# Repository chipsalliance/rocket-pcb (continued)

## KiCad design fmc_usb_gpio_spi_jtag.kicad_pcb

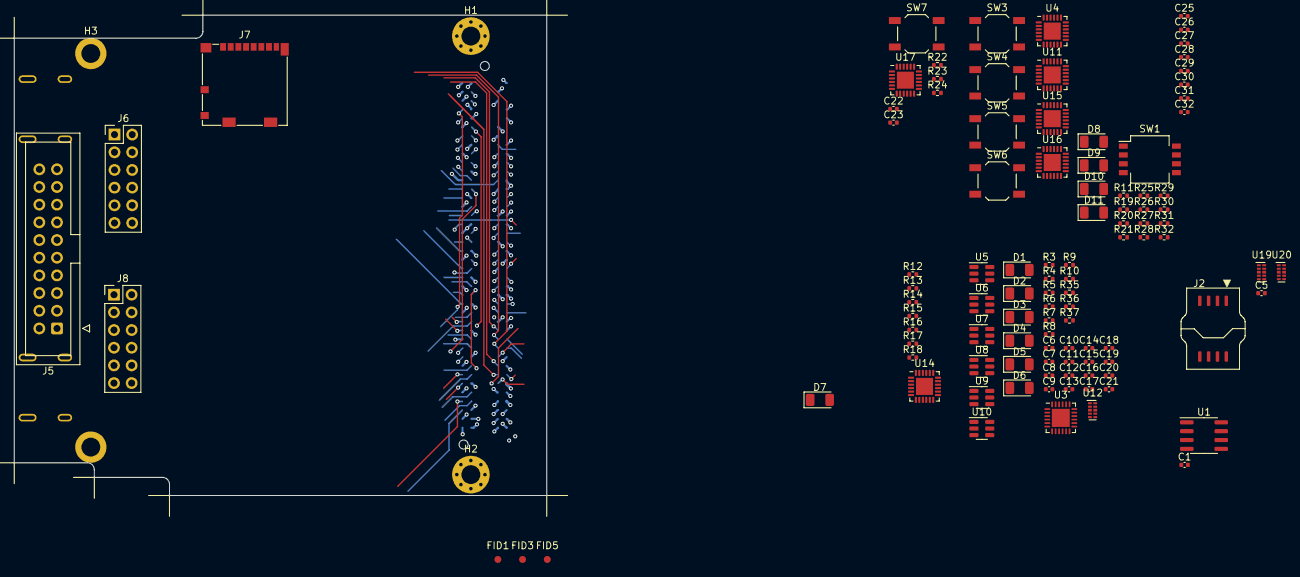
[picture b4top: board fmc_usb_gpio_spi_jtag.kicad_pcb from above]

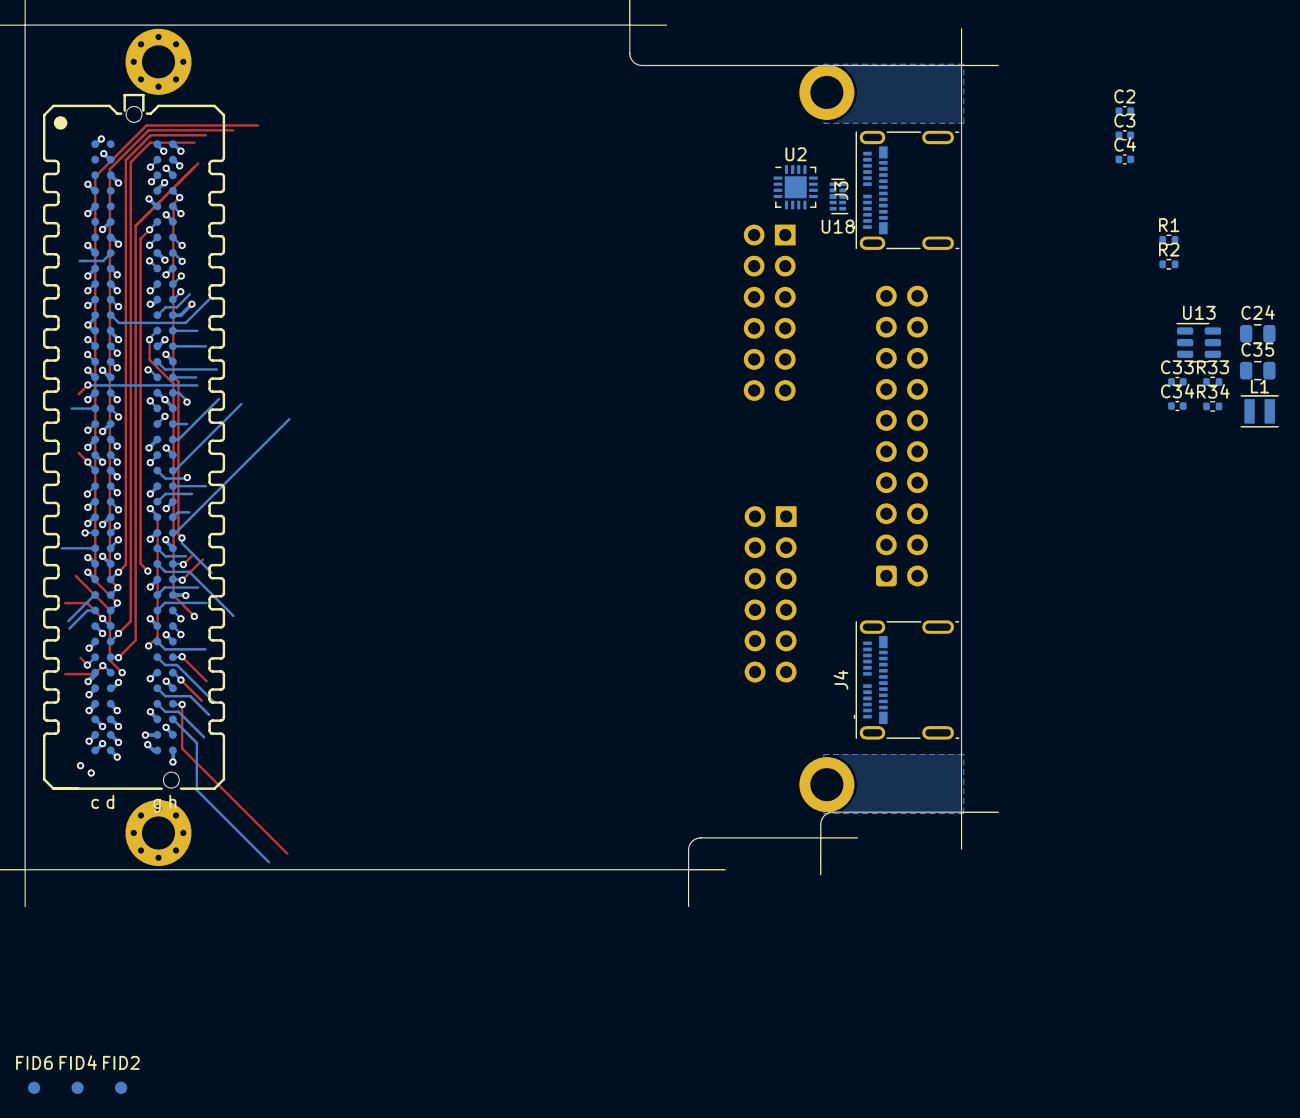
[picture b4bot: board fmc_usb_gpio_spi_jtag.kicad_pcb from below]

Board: 2 copper layers, 76.5 x 69.0 mm, 128 parts (21 on the bottom side), 94 nets.

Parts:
C1, C2, C5, C7, C8, C10, C11, C12, C13, C14, C15, C16, C17, C18, C19, C20, C21, C22, C23, C25, C26, C27, C28, C29, C30, C31, C32: 100n; C_0402_1005Metric
C3: 1u; C_0402_1005Metric
C4, C6, C9: 4.7u; C_0402_1005Metric
C24: 22uF ±20% 35V; C_0805_2012Metric
C33: 22n; C_0402_1005Metric
C34: 22p; C_0402_1005Metric
C35: 22uF; C_0805_2012Metric
D1, D2, D3, D4, D5, D6, D7, D8, D9, D10, D11: NCD1206Y1; LED_1206_3216Metric
FID1, FID2, FID3, FID4, FID5, FID6: 1mm; Fiducial_1mm_Mask2mm
H1, H2: M2.5; MountingHole_2.7mm_M2.5_Pad_Via
H3, H4: M2.5; MountingHole_2.7mm_M2.5_ISO14580_Pad
J1: SAMTEC_ASP-134604-01; Samtec_FMC_ASP-134604-01_4x40_P1.27mm
J2: ACA-SPI-004-K02; ACA-SPI-004
J3, J4: USB_C_Receptacle; USB_C_Receptacle_Molex_105450-0101
J5: Conn_JTAG_20; IDC-Header_2x10_P2.54mm_Vertical
J6, J8: PM2.54-2x6; PinHeader_2x06_P2.54mm_Vertical
J7: MOLEX 1040310811; microSD_HC_Molex_104031-0811
L1: 4.7uH ±20% 1.6A TFM252012ALMA4R7MTAA; L_Sunlord_SWPA252012S
R1, R2, R3, R4, R35: 5.1k; R_0402_1005Metric
R5, R6, R7, R8, R9, R10, R18, R29, R30, R31, R32: 10k; R_0402_1005Metric
R11, R12, R13, R14, R15, R16, R17, R19, R20, R21, R22, R23, R24, R25, R26, R27, R28, R37: 47k; R_0402_1005Metric
R33: 100k; R_0402_1005Metric
R34: 22k; R_0402_1005Metric
R36: 24k; R_0402_1005Metric
SW1: DSHP04TSGET; SW_DIP_SPSTx04_Slide_KingTek_DSHP04TS_W7.62mm_P1.27mm
SW3, SW4, SW5, SW6, SW7: TL3342F160QG; SW_SPST_TL3342
U1: M24C02-FMN; SOIC-8_3.9x4.9mm_P1.27mm
U2: STUSB03EQR; QFN_B03EQR_STM
U3: CP2104; QFN-24-1EP_4x4mm_P0.5mm_EP2.6x2.6mm
U4, U11, U14, U15, U16, U17: TXS02612RTWR; WQFN-24-1EP_4x4mm_P0.5mm_EP2.45x2.45mm
U5, U6, U7, U8, U9, U10: AIP74LVC1T45GB236TR; SOT-23-6
U12, U18, U19, U20: TPD4E02B04DQA; USON-10_2.5x1.0mm_P0.5mm
U13: MT2492; SOT-23-6

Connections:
/FMC/GA0: J1.C34 (Pin_34), U1.2 (E1)
/FMC/GA1: J1.D35 (d35), U1.1 (E0)
/FMC/SCL: J1.C30 (Pin_30), U1.6 (SCL)
/FMC/SDA: J1.C31 (Pin_31), U1.5 (SDA)
/GPIO/HVGPIO0: J6.1, U11.18 (DAT0B0)
/GPIO/HVGPIO1: J6.2, U11.16 (DAT1B0)
/GPIO/HVGPIO2: J6.3, U11.23 (DAT2B0)
/GPIO/HVGPIO3: J6.4, U11.22 (DAT3B0)
/GPIO/HVGPIO4: J6.5, U11.20 (CMDB0)
/GPIO/HVGPIO5: J6.6, U4.18 (DAT0B0)
/GPIO/HVGPIO6: J6.7, U4.16 (DAT1B0)
/GPIO/HVGPIO7: J6.8, U4.23 (DAT2B0)
/GPIO/HVGPIO8: J8.1, U4.22 (DAT3B0)
/GPIO/HVGPIO9: J8.2, U4.20 (CMDB0)
/GPIO/HVGPIO10: J8.3, U15.18 (DAT0B0)
/GPIO/HVGPIO11: J8.4, U15.16 (DAT1B0)
/GPIO/HVGPIO12: J8.5, U15.23 (DAT2B0)
/GPIO/HVGPIO13: J8.6, U15.22 (DAT3B0)
/GPIO/HVGPIO14: J8.7, U15.20 (CMDB0)
/GPIO/HVGPIO15: J8.8, U16.18 (DAT0B0)
/GPIO/HVGPIO16: D8.1 (K), R25.1, SW1.1, SW3.2, U16.16 (DAT1B0)
/GPIO/HVGPIO17: D9.1 (K), R26.1, SW1.2, SW4.2, U16.23 (DAT2B0)
/GPIO/HVGPIO18: D10.1 (K), R27.1, SW1.3, SW5.2, U16.22 (DAT3B0)
/GPIO/HVGPIO19: D11.1 (K), R28.1, SW1.4, SW6.2, U16.20 (CMDB0)
/JTAG/SRST: J5.15 (~SRST), R23.2, SW7.2, U17.7 (DAT1A)
/JTAG/TCK: J5.9 (TCK), U17.9 (CLKA)
/JTAG/TDI: J5.5 (TDI), U17.4 (CMDA)
/JTAG/TDO: J5.13 (TDO), U17.3 (DAT3A)
/JTAG/TMS: J5.7 (TMS), U17.1 (DAT2A)
/JTAG/TRST: J5.3 (~TRST), R24.2, U17.6 (DAT0A)
/SDIO/SD_CLK: J7.5 (CLK), U14.19 (CLKB0)
/SDIO/SD_CMD: J7.3 (CMD), R17.1, U14.20 (CMDB0)
/SDIO/SD_DAT0: J7.7 (DAT0), R13.1, U14.18 (DAT0B0)
/SDIO/SD_DAT1: J7.8 (DAT1), R14.1, U14.16 (DAT1B0)
/SDIO/SD_DAT2: J7.1 (DAT2), R15.1, U14.23 (DAT2B0)
/SDIO/SD_DAT3: J7.2 (DAT3/CD), R16.1, U14.22 (DAT3B0)
/SPI FLASH/SPI_FLASH.CLK: J2.6, U20.2 (IO2), U20.9 (NC)
/SPI FLASH/SPI_FLASH.CS: J2.1, U19.1 (IO1), U19.10 (NC)
/SPI FLASH/SPI_FLASH.DI: J2.5, U20.4 (IO3), U20.7 (NC)
/SPI FLASH/SPI_FLASH.DO: J2.2, U19.2 (IO2), U19.9 (NC)
/SPI FLASH/SPI_FLASH.~HOLD: J2.7, U20.1 (IO1), U20.10 (NC)
/SPI FLASH/SPI_FLASH.~WP: J2.3, U19.4 (IO3), U19.7 (NC)
/UART/CP_IO0: U3.14 (TXT/GPIO.0), U5.4 (B)
/UART/CP_IO1: U3.13 (RXT/GPIO.1), U6.4 (B)
/UART/CP_IO2: U3.12 (RS485/GPIO.2), U7.4 (B)
/UART/CP_IO3: U3.11 (GPIO.3), U8.4 (B)
/UART/CP_SUSP: U3.17 (SUSPEND), U9.4 (B)
/UART/CP_~SUSP: U3.15 (~SUSPEND), U10.4 (B)
/USB/D+: J3.A6 (D+), J3.B6 (D+), U2.11 (D+), U18.4 (IO3), U18.7 (NC)
/USB/D-: J3.A7 (D-), J3.B7 (D-), U2.10 (D-), U18.5 (IO4), U18.6 (NC)
GND: C1.2, C2.2, C3.2, C4.2, C5.2, C6.2, C7.2, C8.2, C9.2, C10.2, C11.2, C12.2, C13.2, C14.2, C15.2, C16.2, C17.2, C18.2, C19.2, C20.2, C21.2, C22.2, C23.2, C24.2, C25.2, C26.2, C27.2, C28.2, C29.2, C30.2, C31.2, C32.2, C35.2, H1.1, H2.1, H3.1, H4.1, J1.C1 (Pin_1), J1.C4 (Pin_4), J1.C5 (Pin_5), J1.C8 (Pin_8), J1.C9 (Pin_9), J1.C12 (Pin_12), J1.C13 (Pin_13), J1.C16 (Pin_16), J1.C17 (Pin_17), J1.C20 (Pin_20), J1.C21 (Pin_21), J1.C24 (Pin_24), J1.C25 (Pin_25), J1.C28 (Pin_28), J1.C29 (Pin_29), J1.C32 (Pin_32), J1.C33 (Pin_33), J1.C36 (Pin_36), J1.C38 (Pin_38), J1.C40 (Pin_40), J1.D2 (d2), J1.D3 (d3), J1.D6 (d6), J1.D7 (d7), J1.D10 (d10), J1.D13 (d13), J1.D16 (d16), J1.D19 (d19), J1.D22 (d22), J1.D25 (d25), J1.D28 (d28), J1.D37 (d37), J1.D39 (d39), J1.G1 (g1), J1.G4 (g4), J1.G5 (g5), J1.G8 (g8), J1.G11 (g11), J1.G14 (g14), J1.G17 (g17), J1.G20 (g20), J1.G23 (g23), J1.G26 (g26), J1.G29 (g29), J1.G32 (g32), J1.G35 (g35), J1.G38 (g38), J1.G40 (g40), J1.H2 (h2), J1.H3 (h3), J1.H6 (h6), J1.H9 (h9), J1.H12 (h12), J1.H15 (h15), J1.H18 (h18), J1.H21 (h21), J1.H24 (h24), J1.H27 (h27), J1.H30 (h30), J1.H33 (h33), J1.H36 (h36), J1.H39 (h39), J2.4, J3.A1 (GND), J3.A12 (GND), J3.B1 (GND), J3.B12 (GND), J3.S1 (SHIELD), J4.A1 (GND), J4.A12 (GND), J4.B1 (GND), J4.B12 (GND), J4.S1 (SHIELD), J5.4 (GND), J5.6 (GND), J5.8 (GND), J5.10 (GND), J5.12 (GND), J5.14 (GND), J5.16 (GND), J5.18 (GND), J5.20 (GND), J6.9, J6.10, J7.6 (VSS), J7.9 (DET_B), J7.11 (SHIELD), J8.9, J8.10, R1.1, R2.1, R3.1, R4.1, R5.2, R6.2, R7.2, R8.2, R9.2, R10.2, R11.1, R12.1, R19.1, R20.1, R21.1, R22.1, R34.1, R37.1, SW1.5, SW1.6, SW1.7, SW1.8, SW3.1, SW4.1, SW5.1, SW6.1, SW7.1, U1.3 (E2), U1.4 (VSS), U1.7 (~WC), U2.6 (GND), U3.2 (GND), U3.25 (GND), U4.2 (GND), U4.11 (GND), U4.25 (GND), U5.2 (GND), U5.5 (DIR), U6.2 (GND), U6.5 (DIR), U7.2 (GND), U7.5 (DIR), U8.2 (GND), U8.5 (DIR), U9.2 (GND), U9.5 (DIR), U10.2 (GND), U10.5 (DIR), U11.2 (GND), U11.11 (GND), U11.25 (GND), U12.3 (G), U12.8 (G), U13.1 (GND), U14.2 (GND), U14.11 (GND), U14.25 (GND), U15.2 (GND), U15.11 (GND), U15.25 (GND), U16.2 (GND), U16.11 (GND), U16.25 (GND), U17.2 (GND), U17.11 (GND), U17.25 (GND), U18.3 (G), U18.8 (G), U19.3 (G), U19.8 (G), U20.3 (G), U20.8 (G)
unnamed: C3.1, U2.12 (VTRM)
unnamed: C4.1, J3.A4 (VBUS), J3.A9 (VBUS), J3.B4 (VBUS), J3.B9 (VBUS), U2.14 (VBUS)
unnamed: D1.2 (A), U5.3 (A)
unnamed: D1.1 (K), R5.1
unnamed: D2.2 (A), U6.3 (A)
unnamed: D2.1 (K), R6.1
unnamed: D3.2 (A), U7.3 (A)
unnamed: D3.1 (K), R7.1
unnamed: D4.2 (A), U8.3 (A)
unnamed: D4.1 (K), R8.1
unnamed: D5.2 (A), U9.3 (A)
unnamed: D5.1 (K), R9.1
unnamed: D6.2 (A), U10.3 (A)
unnamed: D6.1 (K), R10.1
unnamed: D7.1 (K), R18.2
unnamed: D8.2 (A), R29.2
unnamed: D9.2 (A), R30.2
unnamed: D10.2 (A), R31.2
unnamed: D11.2 (A), R32.2
unnamed: J1.D30 (d30), J1.D31 (d31)
unnamed: J3.A5 (CC1), R1.2
unnamed: J3.B5 (CC2), R2.2
unnamed: J4.A5 (CC1), R3.2
unnamed: J4.B5 (CC2), R4.2
unnamed: J4.A4 (VBUS), J4.A9 (VBUS), J4.B4 (VBUS), J4.B9 (VBUS), R36.2
unnamed: J7.10 (DET_A), R18.1
unnamed: R36.1, R37.2, U3.8 (VBUS)
unnamed: C9.1, U3.16 (VPP)
unnamed: R35.1, U3.9 (~RST)
unnamed: R19.2, U4.9 (CLKA), U4.24 (SEL)
unnamed: R11.2, U11.9 (CLKA), U11.24 (SEL)
unnamed: J4.A6 (D+), J4.B6 (D+), U3.3 (D+), U12.4 (IO3), U12.7 (NC)
unnamed: J4.A7 (D-), J4.B7 (D-), U3.4 (D-), U12.5 (IO4), U12.6 (NC)
unnamed: C33.2, U13.6 (BST)
unnamed: C34.1, R33.1, R34.2, U13.4 (FB)
unnamed: C33.1, L1.1, U13.2 (SW)
unnamed: R12.2, U14.24 (SEL)
unnamed: R20.2, U15.9 (CLKA), U15.24 (SEL)
unnamed: R21.2, U16.9 (CLKA), U16.24 (SEL)
unnamed: R22.2, U17.24 (SEL)
P3V3: C25.1, C26.1, C27.1, C28.1, C29.1, C30.1, C31.1, C32.1, J6.11, J6.12, J8.11, J8.12, R25.2, R26.2, R27.2, R28.2, R29.1, R30.1, R31.1, R32.1, U4.5 (VCCA), U4.17 (VCCB1), U4.21 (VCCB0), U11.5 (VCCA), U11.17 (VCCB1), U11.21 (VCCB0), U15.5 (VCCA), U15.17 (VCCB1), U15.21 (VCCB0), U16.5 (VCCA), U16.17 (VCCB1), U16.21 (VCCB0)
P12V: C24.1, U13.3 (IN), U13.5 (EN)
VDD: C1.1, C2.1, C5.1, C6.1, C7.1, C8.1, C10.1, C11.1, C12.1, C13.1, C14.1, C15.1, C16.1, C17.1, C18.1, C19.1, C20.1, C21.1, C22.1, C23.1, C34.2, C35.1, D7.2 (A), J1.C35 (Pin_35), J1.C37 (Pin_37), J1.C39 (Pin_39), J1.D32 (d32), J1.D36 (d36), J1.D38 (d38), J1.D40 (d40), J1.G39 (g39), J1.H40 (h40), J2.8, J5.1 (VTREF), J7.4 (VDD), L1.2, R13.2, R14.2, R15.2, R16.2, R17.2, R23.1, R24.1, R33.2, R35.2, U1.8 (VCC), U2.8 (RSEL), U2.15 (VIF), U3.5 (VIO), U3.6 (VDD), U3.7 (REGIN), U5.1 (VCCA), U5.6 (VCCB), U6.1 (VCCA), U6.6 (VCCB), U7.1 (VCCA), U7.6 (VCCB), U8.1 (VCCA), U8.6 (VCCB), U9.1 (VCCA), U9.6 (VCCB), U10.1 (VCCA), U10.6 (VCCB), U14.5 (VCCA), U14.17 (VCCB1), U14.21 (VCCB0), U17.5 (VCCA), U17.17 (VCCB1), U17.21 (VCCB0)

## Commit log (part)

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2023-03-31 README.md: fix link to fmc_basic_peripheral
2023-03-31 README.md: format markdown table
2023-04-03 *.kicad_pcb: update layout, change cp2104 to USB bus powered
2023-04-03 sdio.kicad_sch: change sdcard detect LED resistor to 6.8k Ohm
2023-04-03 uart.kicad_sch: for easy wiring, swap D5 and D6
2023-04-03 usb.kicad_sch: rename USB_VBUS to USB_FS_VBUS
2023-04-03 *.kicad_pcb: update layout for LED swap
2023-04-07 *.kicad_pcb: add dummy pattern
2023-04-07 fpga/vcu118/*: Add FPGA project for rough testing of FMC boards
2023-04-07 uart.kicad_sch: replace cp2104 with ch9102f
    After testing, cp2104 is unstable at the moment of power-on,
    so it is replaced with ch9102f to fix this issue.
2023-04-07 *.kicad_sch: update footprint for QFN*
2023-04-10 top.xdc: Fix pin mapping issue for UART xdc
    - Fix UART communication issue by swapping `uart_rx` and `uart_tx` pins in `top.xdc`
2023-04-10 fmc.kicad_sch: Improve FMC peripheral schematic
    - Add annotation for UART crossing
2023-04-23 jtag.kicad_sch: move VADJ annotation text
    - Update and improve JTAG schematic file
2023-04-23 *pcb: Update PCB layout design for FMC peripherals.
    - Connect user RESET to CH9102F
    - Implement significant changes to [fmc_basic_peripheral/fmc_usb_gpio_spi_jtag.kicad_pcb]
    - Fix known bugs within affected files
    - Enhance overall user experience and functionality
2023-04-23 usb.kicad_sch: add LED for usb VBUS power and ~{SUSP}
    - add orange LED for usb VBUS
    - add yellow LED for usb ~{SUSP}
2023-04-23 uart.kicad_sch: change D5 to NCD1206Y1
    - fix color of D5
2023-04-24 usb.kicad_sch: add matching resistor to STUSB03E
2023-04-24 *.kicad_pcb: add matching resistor to STUSB03E
    - update layout of STUSB03E
    - DRC clean
2023-04-24 *.kicad_pcb: bump version to 1.0.5
    - DRC clean, update version to match the schematic
2023-05-09 *.kicad_pcb: clean DRC for kicad 7.0.2
2023-05-09 *.kicad_pro: ignore silk_over_copper check
2023-05-09 fmc_basic_peripheral: rotate SW1, bump to 1.0.6
2023-05-11 fmc_basic_peripheral/fpga/vcu118/.gitignore: ignore .cache
2023-05-11 fmc_basic_peripheral/*/openocd.cfg: use new command
2023-05-17 fmc_basic_peripheral/*/top.v: fix reset and mode switch logic
2023-05-17 fmc_basic_peripheral/*/top.v: add sdio xdc and test square wave
2023-05-17 .gitmodules: update submodule link
2023-05-17 uart.kicad_sch: merge CP_IO into GPIO
2023-05-17 gpio.kicad_sch: change GPIO range to [0..23]
2023-05-17 README.md: add index
2023-05-17 *.kicad_sch: fix mounting hole footprint
2023-05-17 *.kicad_sch: expand gpio to [0..31]
2023-05-17 *.kicad_pcb: pre-place devices
    Pre place user key, led, micro-sd socket, etc.
2023-05-17 *.*: finish flash and sdio layout
2023-05-17 Vowstar_Interface*: add stusb3 symbol and footprint
2023-05-17 usb.kicad_sch: add stusb fs transceiver symbol
2023-05-17 template/chipsalliance.kicad_wks: add template of chipsalliance
2023-05-17 sdio.kicad_sch: add SDIO bus lable
2023-05-17 *.kicad_pcb: apply schematic change, fix jtag
2023-05-17 *.kicad_pcb: add stackup table
2023-05-17 *.kicad_pcb: import GX0011D to pcb
2023-05-17 fmc.kicad_sch: fix power flag
2023-05-17 */*: change lib id to CHIPSAlliance
2023-05-17 *.kicad_wks: remove useless TEXT
2023-05-17 uart.kicad_sch: reorder bus alias
2023-05-17 spi_flash.kicad_sch: finished spi flash schematic
2023-05-17 jtag.kicad_sch: fix TRST and SRST polarity
2023-05-17 *.kicad_pcb: add via sealring at board edge
2023-05-17 library: add mounting holes and fiducials
2023-05-17 {library,sdio.kicad_sch}: fix microSD contact style
    Change the microSD contact on the opposite side to a dashed line
2023-05-17 *.kicad_pcb: fix bug of U26, disconnect the CMDA pin
2023-05-17 usb.kicad_sch: fix USB polarity of D+ and D-
2023-05-17 power.kicad_sch: change voltage to 5V
2023-05-17 *.kicad_pcb: import and fix power netlist
2023-05-17 fmc_usb_gpio_spi_jtag.kicad_sch: update fiducial and holes
2023-05-17 *.kicad_sch: fix sheet pin type
2023-05-17 library: add missing GND pin of TXS02612RTWR
2023-05-17 fmc_usb_gpio_spi_jtag.*: update top symbol
2023-05-17 CMakeLists.txt: add python-bom file to PROJECT_PRODUCTION_FILES
2023-05-17 spi_flash.kicad_sch: add signal annotation
2023-05-17 *.kicad_sch: fix GPIO sheet pins
2023-05-17 *{dru,pcb,pro}: fix DRC errors
2023-05-17 */*: restruct project, move * to fmc_basic_peripheral
2023-05-17 *.kicad_dru: fix design rule, add usb net class design rule
2023-05-17 *.kicad_pcb: finish 5V power layout
2023-05-17 fmc.kicad_sch: relink symbol form libraries
2023-05-17 *.kicad_pcb: complete the JTAG signal layout
2023-05-17 sym-lib-table: add mechanical library
2023-05-17 *.kicad_sch: add schematic placeholder of gpio,jtag,power,sdio,spi
2023-05-17 jtag.kicad_sch: use TXS02612RTWR as level shifter
2023-05-17 sym-lib-table: add Logic and Regulator_Switching
2023-05-17 *.kicad_pcb: import netlist form schematic
2023-05-17 power.kicad_sch: add MT2492 power IC
2023-05-17 *.*: add design rule file of PCB
2023-05-17 *.kicad_pcb: add teardrop and enhanced power
2023-05-17 *.kicad_pcb: import schematic to PCB
2023-05-17 fmc_usb_gpio_spi_jtag.kicad_sch: change mounting holes
2023-05-17 *.*: bump version to 1.0.1
2023-05-17 *.kicad_sch: connect GX0011 thermometer sensor
2023-05-17 {library,fp-lib-table}: add FMC MountingHole library
2023-05-17 *.kicad_sch: add CHIPSAlliance_ prefix for footprint
2023-05-17 *.kicad_sch: make vadj textbox wider
2023-05-17 gpio.kicad_sch: use TXS02612RTWR as level shifter
2023-05-17 jtag.kicad_sch: add Conn_JTAG_20
2023-05-17 library: add new symbols of power/levelshifter/connectors
2023-05-17 usb.kicad_sch: finished usb schematic
2023-05-17 i3c.kicad_sch: add i3c bus label
2023-05-17 *.kicad_pcb: annotate PMODs and keys
    Optimize silk screen, add QR code
2023-05-17 gpio.kicad_sch: fix bug of U26, disconnect the CMDA pin
2023-05-17 *.kicad_sch: ERC clean
2023-05-17 fmc.kicad_sch: add signal annotation, use new template
2023-05-17 */*: Initial commit
2023-05-17 {*-table,library}: add CHIPSAlliance_ prefix
2023-05-17 uart.kicad_sch: update usb connector symbol
2023-05-17 *.kicad_pcb: pre-placed components
2023-05-17 fmc.kicad_sch: add hierarchical_label for power and ground
2023-05-17 Vowstar_*->library: move libraries to gitmodule
2023-05-24 fmc_basic_peripheral/library: fix submodule link
2023-12-07 .gitmodules: fix library submodule name
    - Change [submodule "library"] to [submodule "fmc_basic_peripheral/library"]
2023-12-07 fmc_basic_peripheral: fix GPIO PMOD schematic
    - Fix PMOD symbol pin order
    - Followed Digilent Pmod Interface Specification 1.2.0
2023-12-07 fmc_basic_peripheral: bump to 1.0.7, fix ERC
2023-12-07 pmod_microsd: init project, draft schematic
    - Add initial schematic with Sifive's proposed changes
2023-12-08 pmod_microsd/{fp,sym}-lib-table: add Power_Protection library
    - Add CHIPSAlliance_Package_SON footprint library to project
    - Add CHIPSAlliance_Power_Protection symbol library to project
2023-12-08 pmod_microsd: annotate the components
    - Annotate various components so that components have unique references
2023-12-08 pmod_microsd: add PWR_FLAG to VDD and GND, ERC clean
    - Add PWR_FLAG to 3P3V (VDD)
    - Add PWR_FLAG to GND
    - ERC Clean
2023-12-09 pmod_microsd/*.kicad_pcb: PCB outline definition
    - Complete PCB outline and size definition
    - Arrange silk screen
    - Arrange text objects
2023-12-09 pmod_microsd/*.kicad_pcb: Complete PCB layout and routing
    - Complete PCB layout
    - Complete PCB routing
    - Complete PCB silk screen placement
    - LVS comparison successful
    - DRC cleared
2023-12-09 pmod_microsd: add CMakeLists.txt to generate production data
    - cmake -B build -G Ninja
    - cmake --build build
2023-12-09 pmod_microsd/README.md: Add brief documentation
    - Add a brief description
    - Add pin mapping relationship about PMOD and VCU118
    - Added documentation for LED indication
    - Add special pin description
2023-12-09 pmod_microsd/README.md: fix error in LED description
    - Swap power and card detection description
2023-12-09 fmc_basic_peripheral: Update CMakeLists for KiCad Upgrade
    This commit updates the CMakeLists.txt file in the
    fmc_basic_peripheral project to align with the latest KiCad
    version. Changes include:
    1. Modified gerber export command to include 'User.Drawings' in
    the layer list.
    2. Adjusted drill export command to use '--generate-map' and
2023-12-11 .gitignore: exclude build artifacts and python venv
    - Add /bom, /build, /production directories
    - Exclude Python virtual env folder .venv/
2024-02-28 fmc_basic_peripheral: Migrate to kicad8
    - Migrate schematics to kicad8
    - Migrate PCB to kicad8
    - Clean ERC
    - Clean LVS and DRC
2024-02-28 fmc_basic_peripheral: add erc and drc to CMakeLists.txt
    - add erc and drc custom_target and custom_command
    - use these command to check erc and drc:
    cmake -G Ninja -B build
    cmake --build build --target erc
    cmake --build build --target drc
2024-02-28 fmc_basic_peripheral: update SOT-23-5 footprint and fix DRC
2024-02-28 github: Automate CI process for all subdirectories
    - Replaced static directory path with dynamic listing
    - Implemented loop to process all subdirectories
    - Each directory now runs full build and validation sequence
2024-02-29 pmod_microsd: Optimize bom export
2024-02-29 github: Update tag base name extraction in release workflow
    - Modify logic to extract base name from Git tag
    - Replace deprecated set-output with GITHUB_ENV for variables
2024-03-01 ADD: add Gerber files
2024-03-03 fmc_basic_peripheral: require kicad 8
    - README.md: kicad 7 -> kicad 8
2024-03-04 fpga_candelabra: rename project
2024-03-07 Candelabra: Place all FPGA symbols
2024-03-19 Bump library
2024-03-21 FIX: fix C7 placement issue
2024-04-07 fpga_candelabra: reorganize fpga io and mgt by SLR
    - Rename sch sheets
    - Add prelimary DDR and PCIE Bank/Quad allocation
2024-04-09 pmod_microsd/CMakeLists.txt: require kicad 8
    - bump kicad 7 -> kicad 8
2024-04-09 REFACTOR: rename with prefix 'pmod_'
2024-04-09 ADD: add project source code
2024-04-21 fpga_candelabra: fix minor issues in ddr sch
2024-04-21 fpga_candelabra: add clock pll, refactor fmc power
2024-04-21 fpga_candelabra: bump library
2024-05-26 fmc_sdram: Add SDRAM FMC
2024-05-30 README.md: Update README with FMC_SDRAM project introduction
    - Added a new project FMC_SDRAM to the project introduction table.
2024-06-22 fmc_sdram: fix package for SN74AVCH16T245GR
2024-11-01 fpga_candelabra: major revision
    * Finish DDR4 & QSFP+ & PCIe layout
    * Change FMC to LPC
    * Add mikroBUS extension
    * 12V input & PDN updates
    * FPGA config updates
2024-11-11 fpga_candelabra: fix cmake layers
2024-12-09 fpga_candelabra: add ground copper pours for DFM
2025-01-01 fpga_candelabra: fix wrong VCCINT pin number
2025-01-18 fpga_candelabra: use LMK03328 PLL
2025-02-04 fpga_candelabra: more bugfixes & improvements for rev 0.2.0
    - Add Digilent JTAG-SMT2-NC onboard
    - Add fan controller & 4pin fan header
    - Use 9pin header for USB2.0
    - Misc fixes for structure
2026-04-06 fpga_candelabra: exclude pcie edge conn from BOM
2026-04-06 fpga_candelabra: update to kicad 9.0
2026-04-06 github: upgrade CI to kicad 10 and ubuntu 24.04, fix BOM export
2026-04-06 gitignore: add .history directory
2026-04-06 fmc_sdram: fix DRC violations and adjust thermal relief settings
2026-04-06 library: update submodule to fix remaining .wrl references
2026-04-06 github: restore apt cache for kicad packages
2026-05-21 fmc_sdram: tie dqm level shifter dir pins to vadj and fix pcb
2026-05-21 github: only run kicad checks on directories touched by the change
2026-05-21 github: allow release-action to update existing release on tag re-push
2026-05-21 fpga_candelabra: ignore j3 keepout false positives reported by kicad 10
